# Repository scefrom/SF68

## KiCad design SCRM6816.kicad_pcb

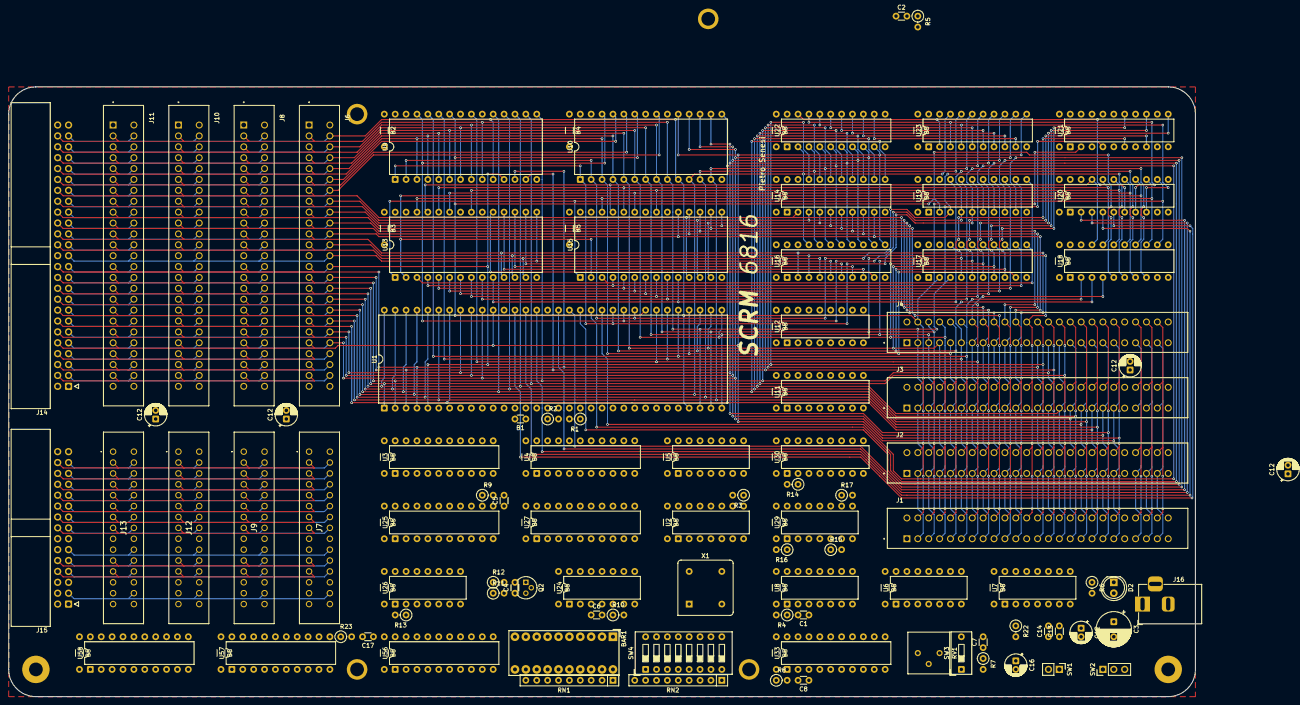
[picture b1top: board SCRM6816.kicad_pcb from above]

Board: 2 copper layers, 276.9 x 142.2 mm, 134 parts (0 on the bottom side), 190 nets.

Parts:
B1: 100nF; C_Disc_D3.0mm_W1.6mm_P2.54mm
B2, B3, B4, B5, B5#2, B5#3, B5#4, B5#5, B5#6, B5#7, B5#8, B5#9, B5#10, B5#11, B5#12, B5#13, B5#14, B5#15, B5#16, B5#17, B5#18, B5#19, B5#20, B5#21, B5#22, B5#23, B5#24, B5#25, B5#26, B5#27, B5#28, B5#29: C_Disc_D3.0mm_W1.6mm_P7.62mm
BAR1: HDSP-4830_2; HDSP-48xx
C1, C2, C5, C6, C8, C17: 22pF; C_Disc_D3.0mm_W1.6mm_P2.54mm
C3: 100uF; CP_Radial_D8.0mm_P3.50mm
C4: 220pF; C_Disc_D3.0mm_W1.6mm_P2.54mm
C7: 1uF; C_Disc_D3.0mm_W1.6mm_P2.54mm
C12, C12#2, C12#3, C12#4, C12#5, C16: 10uF; CP_Radial_D5.0mm_P2.00mm
C13: 330nF; C_Disc_D3.0mm_W1.6mm_P2.54mm
C14: 100nF; C_Disc_D3.0mm_W1.6mm_P2.54mm
D2: LED_Filled; LED_D5.0mm
J1: ramslot1; TE_1-5530843-6
J2: ramslot2; TE_1-5530843-6
J3: ramslot3; TE_1-5530843-6
J4: ramslot4; TE_1-5530843-6
J6: perslot1ad; TE_1-5530843-6
J7: perslot1c; 55308432
J8: perslot2ad; TE_1-5530843-6
J9: perslot2c; 55308432
J10: perslot3ad; TE_1-5530843-6
J11: perslot4ad; TE_1-5530843-6
J12: perslot3c; 55308432
J13: perslot4c; 55308432
J14: peridcad; IDC-Header_2x25_P2.54mm_Horizontal
J15: peridcc; IDC-Header_2x15_P2.54mm_Horizontal
J16: pwrjack; BarrelJack_Horizontal
M2, M2#2, M2#3, M2#4, M2#5, M2#6: MountingHole_3.2mm_M3_Pad
Q2: NPN; TO-92
R1, R2, R3, R8, R13, R14: 4k7; R_Axial_DIN0207_L6.3mm_D2.5mm_P2.54mm_Vertical
R4: 20k; R_Axial_DIN0207_L6.3mm_D2.5mm_P2.54mm_Vertical
R5, R23: 1k22; R_Axial_DIN0207_L6.3mm_D2.5mm_P2.54mm_Vertical
R6, R7: 1k; R_Axial_DIN0207_L6.3mm_D2.5mm_P2.54mm_Vertical
R9, R10: 2k; R_Axial_DIN0207_L6.3mm_D2.5mm_P2.54mm_Vertical
R11, R12, R15, R16, R17: 10k; R_Axial_DIN0207_L6.3mm_D2.5mm_P2.54mm_Vertical
R22: 14k7; R_Axial_DIN0207_L6.3mm_D2.5mm_P2.54mm_Vertical
RN1: 1k; R_Array_SIP9
RN2: 10k; R_Array_SIP9
RV1: 5k; Potentiometer_Bourns_3386P_Vertical
SW1: ressw; PinHeader_1x02_P2.54mm_Vertical
SW2: pwrsw; PinHeader_1x03_P2.54mm_Vertical
SW3: timersw; SW_DIP_SPSTx01_Slide_9.78x4.72mm_W7.62mm_P2.54mm
SW4: SW_DIP_x08; SW_DIP_SPSTx08_Slide_9.78x22.5mm_W7.62mm_P2.54mm
U1: 68HC000P16; DIP-64_W22.86mm
U2: 74HC04; DIP-14_W7.62mm
U3, U4, U21, U56: 74HC688; DIP-20_W7.62mm
U5: 74HC4075; DIP-14_W7.62mm
U6, U29: 74HC32; DIP-14_W7.62mm
U7, U26: 74HC14; DIP-14_W7.62mm
U8: 74HC05; DIP-14_W7.62mm
U9, U10: 28C256; DIP-28_W15.24mm
U11, U12: 74HC157; DIP-16_W7.62mm
U13, U15: AS7C256C-15PCN; DIP-28_W15.24mm
U14, U16: 74HC245; DIP-20_W7.62mm
U17, U18, U19, U20, U23, U27, U33, U58: 74HC541; DIP-20_W7.62mm
U22, U57: 74HC573; DIP-20_W7.62mm
U24: 74HC08; DIP-14_W7.62mm
U25: 74HC273; DIP-20_W7.62mm
U30: 74HC139; DIP-16_W7.62mm
X1: CXO_DIP8_16MHz; Oscillator_DIP-8

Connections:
+5V: B1.1, B2.1, B3.1, B4.1, B5.1, B5#2.1, B5#3.1, B5#4.1, B5#5.1, B5#6.1, B5#7.1, B5#8.1, B5#9.1, B5#10.1, B5#11.1, B5#12.1, B5#13.1, B5#14.1, B5#15.1, B5#16.1, B5#17.1, B5#18.1, B5#19.1, B5#20.1, B5#21.1, B5#22.1, B5#23.1, B5#24.1, B5#25.1, B5#26.1, B5#27.1, B5#28.1, B5#29.1, C3.1, C12.1, C12#2.1, C12#3.1, C12#4.1, C12#5.1, C13.2, C14.2, D2.2 (A), J1.41, J1.42, J2.41, J2.42, J3.41, J3.42, J4.41, J4.42, J7.17, J7.18, J7.19, J9.17, J9.18, J9.19, J12.17, J12.18, J12.19, J13.17, J13.18, J13.19, J15.12, J15.13, J15.14, R1.1, R2.1, R3.1, R8.1, R13.1, R14.1, R22.1, RN2.1 (common), SW2.2 (B), U1.12 (BGACK), U1.13 (BR), U1.14 (VCC), U1.21 (VPA), U1.22 (BERR), U1.25 (IPL0), U1.49 (VCC), U2.14 (VCC), U3.18 (R7), U3.20 (VCC), U4.3 (R0), U4.5 (R1), U4.7 (R2), U4.9 (R3), U4.12 (R4), U4.14 (R5), U4.16 (R6), U4.18 (R7), U4.20 (VCC), U5.14 (VDD), U6.14 (VCC), U7.14 (VCC), U8.14 (VCC), U9.28 (VCC), U10.28 (VCC), U11.10 (I1c), U11.16 (VCC), U12.3 (I1a), U12.5 (I0b), U12.10 (I1c), U12.11 (I0c), U12.13 (I1d), U12.14 (I0d), U12.16 (VCC), U13.28 (VCC), U14.20 (VCC), U15.28 (VCC), U16.20 (VCC), U17.20 (VCC), U18.9 (A7), U18.20 (VCC), U19.20 (VCC), U20.9 (A7), U20.20 (VCC), U21.20 (VCC), U22.20 (VCC), U23.20 (VCC), U24.14 (VCC), U25.18 (D7), U25.20 (VCC), U26.14 (VCC), U27.8 (A6), U27.20 (VCC), U29.14 (VCC), U30.16 (VCC), U33.8 (A6), U33.20 (VCC), U56.3 (R0), U56.5 (R1), U56.7 (R2), U56.9 (R3), U56.12 (R4), U56.14 (R5), U56.16 (R6), U56.20 (VCC), U57.20 (VCC)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
/AC.~D: J7.5, J9.5, J12.5, J13.5, J15.26, U1.27 (FC1), U24.2, U29.4
/AC.~P: J7.3, J9.3, J12.3, J13.3, J15.28, U1.28 (FC0), U24.1, U29.10
/AC.~U: J7.7, J9.7, J12.7, J13.7, J15.24, U1.26 (FC2), U3.17 (P7)
/A_{1}: J1.4, J2.4, J3.4, J4.4, J6.4, J8.4, J10.4, J11.4, J14.47, U1.29 (A1), U9.10 (A0), U10.10 (A0), U17.2 (A0), U21.2 (P0), U56.2 (P0)
/A_{2}: J1.3, J2.3, J3.3, J4.3, J6.3, J8.3, J10.3, J11.3, J14.48, U1.30 (A2), U9.9 (A1), U10.9 (A1), U17.3 (A1), U21.4 (P1), U56.4 (P1)
/A_{3}: J1.6, J2.6, J3.6, J4.6, J6.6, J8.6, J10.6, J11.6, J14.45, U1.31 (A3), U9.8 (A2), U10.8 (A2), U17.4 (A2), U21.6 (P2), U56.6 (P2)
/A_{4}: J1.5, J2.5, J3.5, J4.5, J6.5, J8.5, J10.5, J11.5, J14.46, U1.32 (A4), U9.7 (A3), U10.7 (A3), U17.5 (A3), U21.8 (P3), U56.8 (P3)
/A_{5}: J1.8, J2.8, J3.8, J4.8, J6.8, J8.8, J10.8, J11.8, J14.43, U1.33 (A5), U9.6 (A4), U10.6 (A4), U17.6 (A4), U21.11 (P4), U56.11 (P4)
/A_{6}: J1.7, J2.7, J3.7, J4.7, J6.7, J8.7, J10.7, J11.7, J14.44, U1.34 (A6), U9.5 (A5), U10.5 (A5), U17.7 (A5), U21.13 (P5), U56.13 (P5)
/A_{7}: J1.10, J2.10, J3.10, J4.10, J6.10, J8.10, J10.10, J11.10, J14.41, U1.35 (A7), U9.4 (A6), U10.4 (A6), U17.8 (A6), U21.15 (P6), U56.15 (P6)
/A_{8}: J1.9, J2.9, J3.9, J4.9, J6.9, J8.9, J10.9, J11.9, J14.42, U1.36 (A8), U4.2 (P0), U9.3 (A7), U10.3 (A7), U17.9 (A7)
/A_{9}: J1.12, J2.12, J3.12, J4.12, J6.12, J8.12, J10.12, J11.12, J14.39, U1.37 (A9), U4.4 (P1), U9.25 (A8), U10.25 (A8), U18.2 (A0)
/A_{10}: J1.11, J2.11, J3.11, J4.11, J6.11, J8.11, J10.11, J11.11, J14.40, U1.38 (A10), U4.6 (P2), U9.24 (A9), U10.24 (A9), U18.3 (A1)
/A_{11}: J1.14, J2.14, J3.14, J4.14, J6.14, J8.14, J10.14, J11.14, J14.37, U1.39 (A11), U4.8 (P3), U9.21 (A10), U10.21 (A10), U18.4 (A2)
/A_{12}: U1.40 (A12), U4.11 (P4), U9.23 (A11), U10.23 (A11), U18.5 (A3), U19.2 (A0)
/A_{13}: U1.41 (A13), U4.13 (P5), U9.2 (A12), U10.2 (A12), U18.6 (A4), U19.3 (A1)
/A_{14}: U1.42 (A14), U4.15 (P6), U9.26 (A13), U10.26 (A13), U18.7 (A5), U19.4 (A2)
/A_{15}: U1.43 (A15), U4.17 (P7), U9.1 (A14), U10.1 (A14), U18.8 (A6), U19.5 (A3)
/A_{16}: U1.44 (A16), U2.3, U5.2, U5.4, U19.6 (A4)
/A_{17}: U1.45 (A17), U3.2 (P0), U19.7 (A5)
/A_{18}: U1.46 (A18), U3.4 (P1), U19.8 (A6)
/A_{19}: U1.47 (A19), U3.6 (P2), U19.9 (A7)
/A_{20}: U1.48 (A20), U3.8 (P3), U20.2 (A0)
/A_{21}: U1.50 (A21), U3.11 (P4), U20.3 (A1)
/A_{22}: U1.51 (A22), U3.13 (P5), U20.4 (A2)
/A_{23}: U1.52 (A23), U3.15 (P6), U20.5 (A3)
/BE.I: C6.1, U3.1 (G), U24.3, U26.9
/BE.~ET: U5.10, U11.1 (S), U12.1 (S)
/BE.~E: U5.6, U6.2, U6.4, U7.3
/BE.~IO: J6.46, J8.46, J10.46, J11.46, J14.5, U5.9, U21.17 (P7), U56.17 (P7)
/BE.~M: J6.45, J8.45, J10.45, J11.45, J14.6, U2.2, U11.3 (I1a), U11.6 (I1b), U30.14 (A0)
/CLK: J7.28, J9.28, J12.28, J13.28, J15.3, U1.15 (CLK), X1.5 (OUT)
/DIR.~R: J6.47, J8.47, J10.47, J11.47, J14.4, U7.8, U9.22 (~OE), U10.22 (~OE), U11.14 (I0d), U23.1 (G1), U29.12, U58.1 (G1)
/DIR.~W: J6.48, J8.48, J10.48, J11.48, J14.3, U1.9 (R/W), U6.10, U6.13, U7.9, U9.27 (~WE), U10.27 (~WE), U11.11 (I0c), U14.1 (A->B), U16.1 (A->B), U29.2
/DRD: J1.43, J2.43, J3.43, J4.43, J7.21, J9.21, J12.21, J13.21, J15.10, R3.2, U7.5, U8.2
/DS.~L: J1.47, J2.47, J3.47, J4.47, J6.43, J8.43, J10.43, J11.43, J14.8, U1.8 (LDS), U6.1, U11.2 (I0a)
/DS.~U: J1.48, J2.48, J3.48, J4.48, J6.44, J8.44, J10.44, J11.44, J14.7, U1.7 (UDS), U6.5, U11.5 (I0b), U21.1 (G), U56.1 (G)
/D_{0}: J1.26, J2.26, J3.26, J4.26, J6.28, J8.28, J10.28, J11.28, J14.23, U1.5 (D0), U9.11 (D0), U14.18 (B0), U27.18 (Y0)
/D_{1}: J1.25, J2.25, J3.25, J4.25, J6.27, J8.27, J10.27, J11.27, J14.24, U1.4 (D1), U9.12 (D1), U14.17 (B1), U27.17 (Y1)
/D_{2}: J1.28, J2.28, J3.28, J4.28, J6.30, J8.30, J10.30, J11.30, J14.21, U1.3 (D2), U9.13 (D2), U14.16 (B2), U27.16 (Y2)
/D_{3}: J1.27, J2.27, J3.27, J4.27, J6.29, J8.29, J10.29, J11.29, J14.22, U1.2 (D3), U9.15 (D3), U14.15 (B3), U27.15 (Y3)
/D_{4}: J1.30, J2.30, J3.30, J4.30, J6.32, J8.32, J10.32, J11.32, J14.19, U1.1 (D4), U9.16 (D4), U14.14 (B4), U27.14 (Y4)
/D_{5}: J1.29, J2.29, J3.29, J4.29, J6.31, J8.31, J10.31, J11.31, J14.20, U1.64 (D5), U9.17 (D5), U14.13 (B5), U27.13 (Y5)
/D_{6}: J1.32, J2.32, J3.32, J4.32, J6.34, J8.34, J10.34, J11.34, J14.17, U1.63 (D6), U9.18 (D6), U14.12 (B6), U27.12 (Y6)
/D_{7}: J1.31, J2.31, J3.31, J4.31, J6.33, J8.33, J10.33, J11.33, J14.18, U1.62 (D7), U9.19 (D7), U14.11 (B7), U27.11 (Y7)
/D_{8}: J1.34, J2.34, J3.34, J4.34, J6.36, J8.36, J10.36, J11.36, J14.15, U1.61 (D8), U10.11 (D0), U16.18 (B0), U22.2 (D0), U23.18 (Y0), U57.2 (D0), U58.18 (Y0)
/D_{9}: J1.33, J2.33, J3.33, J4.33, J6.35, J8.35, J10.35, J11.35, J14.16, U1.60 (D9), U10.12 (D1), U16.17 (B1), U22.3 (D1), U23.17 (Y1), U57.3 (D1), U58.17 (Y1)
/D_{10}: J1.36, J2.36, J3.36, J4.36, J6.38, J8.38, J10.38, J11.38, J14.13, U1.59 (D10), U10.13 (D2), U16.16 (B2), U22.4 (D2), U23.16 (Y2), U57.4 (D2), U58.16 (Y2)
/D_{11}: J1.35, J2.35, J3.35, J4.35, J6.37, J8.37, J10.37, J11.37, J14.14, U1.58 (D11), U10.15 (D3), U16.15 (B3), U22.5 (D3), U23.15 (Y3), U57.5 (D3), U58.15 (Y3)
/D_{12}: J1.38, J2.38, J3.38, J4.38, J6.40, J8.40, J10.40, J11.40, J14.11, U1.57 (D12), U10.16 (D4), U16.14 (B4), U22.6 (D4), U23.14 (Y4), U57.6 (D4), U58.14 (Y4)
/D_{13}: J1.37, J2.37, J3.37, J4.37, J6.39, J8.39, J10.39, J11.39, J14.12, U1.56 (D13), U10.17 (D5), U16.13 (B5), U22.7 (D5), U23.13 (Y5), U57.7 (D5), U58.13 (Y5)
/D_{14}: J1.40, J2.40, J3.40, J4.40, J6.42, J8.42, J10.42, J11.42, J14.9, U1.55 (D14), U10.18 (D6), U16.12 (B6), U22.8 (D6), U23.12 (Y6), U57.8 (D6), U58.12 (Y6)
/D_{15}: J1.39, J2.39, J3.39, J4.39, J6.41, J8.41, J10.41, J11.41, J14.10, U1.54 (D15), U10.19 (D7), U16.11 (B7), U22.9 (D7), U23.11 (Y7), U57.9 (D7), U58.11 (Y7)
/E_{0}: J1.13, J2.13, J3.13, J4.13, J6.13, J8.13, J10.13, J11.13, J14.38, U14.2 (A0), U15.11 (D0)
/E_{1}: J1.16, J2.16, J3.16, J4.16, J6.16, J8.16, J10.16, J11.16, J14.35, U14.3 (A1), U15.12 (D1)
/E_{2}: J1.15, J2.15, J3.15, J4.15, J6.15, J8.15, J10.15, J11.15, J14.36, U14.4 (A2), U15.13 (D2)
/E_{3}: J1.18, J2.18, J3.18, J4.18, J6.18, J8.18, J10.18, J11.18, J14.33, U14.5 (A3), U15.15 (D3)
/E_{4}: J1.17, J2.17, J3.17, J4.17, J6.17, J8.17, J10.17, J11.17, J14.34, U14.6 (A4), U15.16 (D4)
/E_{5}: J1.20, J2.20, J3.20, J4.20, J6.20, J8.20, J10.20, J11.20, J14.31, R15.1, U14.7 (A5), U15.17 (D5)
/E_{6}: J1.19, J2.19, J3.19, J4.19, J6.19, J8.19, J10.19, J11.19, J14.32, R16.1, U14.8 (A6), U15.18 (D6)
/E_{7}: J1.22, J2.22, J3.22, J4.22, J6.22, J8.22, J10.22, J11.22, J14.29, R17.1, U14.9 (A7), U15.19 (D7)
/E_{8}: J1.21, J2.21, J3.21, J4.21, J6.21, J8.21, J10.21, J11.21, J14.30, U13.11 (D0), U16.2 (A0)
/E_{9}: J1.24, J2.24, J3.24, J4.24, J6.24, J8.24, J10.24, J11.24, J14.27, U13.12 (D1), U16.3 (A1)
/E_{10}: J6.23, J8.23, J10.23, J11.23, J14.28, U13.13 (D2), U16.4 (A2), U30.3 (A1)
/E_{11}: J6.26, J8.26, J10.26, J11.26, J14.25, U13.15 (D3), U16.5 (A3), U30.2 (A0)
/E_{12}: U13.16 (D4), U16.6 (A4)
/E_{13}: J7.4, J9.4, J12.4, J13.4, J15.27, U13.17 (D5), U16.7 (A5), U29.5
/E_{14}: J7.6, J9.6, J12.6, J13.6, J15.25, U13.18 (D6), U16.8 (A6), U29.1
/E_{15}: J7.8, J9.8, J12.8, J13.8, J15.23, U13.19 (D7), U16.9 (A7), U29.9
/IBSY: J7.20, J9.20, J12.20, J13.20, J15.11, R12.1, U25.19 (Q7), U26.3, U33.19 (G2)
/IRQ_{0}: J7.10, J9.10, J12.10, J13.10, J15.21, U25.3 (D0), U33.18 (Y0)
/IRQ_{1}: J7.9, J9.9, J12.9, J13.9, J15.22, U25.4 (D1), U33.17 (Y1)
/IRQ_{2}: J7.12, J9.12, J12.12, J13.12, J15.19, U25.7 (D2), U33.16 (Y2)
/IRQ_{3}: J7.11, J9.11, J12.11, J13.11, J15.20, U25.8 (D3), U33.15 (Y3)
/IRQ_{4}: J7.14, J9.14, J12.14, J13.14, J15.17, U25.13 (D4), U33.14 (Y4)
/IRQ_{5}: J7.13, J9.13, J12.13, J13.13, J15.18, U25.14 (D5), U33.13 (Y5)
/IRQ_{6}: J7.16, J9.16, J12.16, J13.16, J15.15, U25.17 (D6), U33.12 (Y6)
/IRQ_{7}: J7.15, J9.15, J12.15, J13.15, J15.16, R13.2, U26.1, U33.11 (Y7)
/atu/EA_{0}: U13.10 (A0), U15.10 (A0), U17.18 (Y0), U19.18 (Y0)
/atu/EA_{1}: U13.9 (A1), U15.9 (A1), U17.17 (Y1), U19.17 (Y1)
/atu/EA_{2}: U13.8 (A2), U15.8 (A2), U17.16 (Y2), U19.16 (Y2)
/atu/EA_{3}: U13.7 (A3), U15.7 (A3), U17.15 (Y3), U19.15 (Y3)
/atu/EA_{4}: U13.6 (A4), U15.6 (A4), U17.14 (Y4), U19.14 (Y4)
/atu/EA_{5}: U13.5 (A5), U15.5 (A5), U17.13 (Y5), U19.13 (Y5)
/atu/EA_{6}: U13.4 (A6), U15.4 (A6), U17.12 (Y6), U19.12 (Y6)
/atu/EA_{7}: U13.3 (A7), U15.3 (A7), U17.11 (Y7), U19.11 (Y7)
/atu/EA_{8}: U13.25 (A8), U15.25 (A8), U18.18 (Y0), U20.18 (Y0)
/atu/EA_{9}: U13.24 (A9), U15.24 (A9), U18.17 (Y1), U20.17 (Y1)
/atu/EA_{10}: U13.21 (A10), U15.21 (A10), U18.16 (Y2), U20.16 (Y2)
/atu/EA_{11}: U13.23 (A11), U15.23 (A11), U18.15 (Y3), U20.15 (Y3)
/atu/EA_{12}: U13.2 (A12), U15.2 (A12), U18.14 (Y4), U20.14 (Y4)
/atu/EA_{13}: U13.26 (A13), U15.26 (A13), U18.13 (Y5), U20.13 (Y5)
/atu/EA_{14}: U13.1 (A14), U15.1 (A14), U18.12 (Y6), U20.12 (Y6)
/atu/MOD.~R: U12.7 (Zb), U19.1 (G1), U19.19 (G2), U20.1 (G1), U20.19 (G2)
/atu/MOD.~S: U12.4 (Za), U14.19 (CE), U16.19 (CE), U17.1 (G1), U17.19 (G2), U18.1 (G1), U18.19 (G2)
/atu/PN_{0}: U20.6 (A4), U22.19 (Q0), U23.2 (A0)
/atu/PN_{1}: U20.7 (A5), U22.18 (Q1), U23.3 (A1)
/atu/PN_{2}: U20.8 (A6), U22.17 (Q2), U23.4 (A2)
/atu/PN_{3}: U22.16 (Q3), U23.5 (A3)
/atu/PN_{4}: U22.15 (Q4), U23.6 (A4)
/atu/PN_{5}: U22.14 (Q5), U23.7 (A5)
/atu/PN_{6}: U22.13 (Q6), U23.8 (A6)
/atu/PN_{7}: U22.12 (Q7), U23.9 (A7)
/atu/pidreg/LD: C2.1, U2.8
/atu/pidreg/~S: U6.9, U21.19 (P=R), U23.19 (G2)
/atu/~LS: U11.4 (Za), U15.20 (CE)
/atu/~R: U11.12 (Zd), U13.22 (OE), U15.22 (OE)
/atu/~US: U11.7 (Zb), U13.20 (CE)
/atu/~W: U11.9 (Zc), U13.27 (WE), U15.27 (WE)
/decoder/~IOS: U2.5, U4.19 (P=R), U5.1
/decoder/~SAS: U2.1, U3.19 (P=R), U5.5, U5.8, U5.12
/ram/PDIR.~R: J1.45, J2.45, J3.45, J4.45, U29.11
/ram/PDIR.~W: J1.46, J2.46, J3.46, J4.46, U29.3
/ram/~BKE_{0}: J1.44, U30.4 (O0)
/ram/~BKE_{1}: J2.44, U30.5 (O1)
/ram/~BKE_{2}: J3.44, U30.6 (O2)
/ram/~BKE_{3}: J4.44, U30.7 (O3)
/rom/~LS: U6.3, U9.20 (~CS)
/rom/~US: U6.6, U10.20 (~CS)
/statusreg/LD: C17.1, U2.10
/statusreg/SI_{0}: RN2.2 (R1), SW4.8, U58.2 (A0)
/statusreg/SI_{1}: RN2.3 (R2), SW4.7, U58.3 (A1)
/statusreg/SI_{2}: RN2.4 (R3), SW4.6, U58.4 (A2)
/statusreg/SI_{3}: RN2.5 (R4), SW4.5, U58.5 (A3)
/statusreg/SI_{4}: RN2.6 (R5), SW4.4, U58.6 (A4)
/statusreg/SI_{5}: RN2.7 (R6), SW4.3, U58.7 (A5)
/statusreg/SI_{6}: RN2.8 (R7), SW4.2, U58.8 (A6)
/statusreg/SI_{7}: RN2.9 (R8), SW4.1, U58.9 (A7)
/statusreg/S_{0}: BAR1.1 (A), U57.19 (Q0)
/statusreg/S_{1}: BAR1.2 (A), U57.18 (Q1)
/statusreg/S_{2}: BAR1.3 (A), U57.17 (Q2)
/statusreg/S_{3}: BAR1.4 (A), U57.16 (Q3)
/statusreg/S_{4}: BAR1.5 (A), U57.15 (Q4)
/statusreg/S_{5}: BAR1.6 (A), U57.14 (Q5)
/statusreg/S_{6}: BAR1.7 (A), U57.13 (Q6)
/statusreg/S_{7}: BAR1.8 (A), U57.12 (Q7)
/statusreg/~S: U6.12, U56.19 (P=R), U58.19 (G2)
/~DRD: U1.10 (DTACK), U7.6
/~HALT: J7.23, J9.23, J12.23, J13.23, J15.8, R2.2, U1.17 (HALT), U8.6
/~I_{1}: U1.24 (IPL1), U26.10
/~I_{2}: U1.23 (IPL2), U26.12
/~RES: J7.24, J9.24, J12.24, J13.24, J15.7, R1.2, U1.18 (RESET), U8.4, U24.9
/~RIH: J7.22, J9.22, J12.22, J13.22, J15.9, R14.2, U30.13 (A1)
GND: B1.2, B2.2, B3.2, B4.2, B5.2, B5#2.2, B5#3.2, B5#4.2, B5#5.2, B5#6.2, B5#7.2, B5#8.2, B5#9.2, B5#10.2, B5#11.2, B5#12.2, B5#13.2, B5#14.2, B5#15.2, B5#16.2, B5#17.2, B5#18.2, B5#19.2, B5#20.2, B5#21.2, B5#22.2, B5#23.2, B5#24.2, B5#25.2, B5#26.2, B5#27.2, B5#28.2, B5#29.2, C3.2, C4.1, C5.1, C7.1, C12.2, C12#2.2, C12#3.2, C12#4.2, C12#5.2, C13.1, C14.1, C16.2, J1.1, J1.2, J1.23, J1.49, J1.50, J2.1, J2.2, J2.23, J2.49, J2.50, J3.1, J3.2, J3.23, J3.49, J3.50, J4.1, J4.2, J4.23, J4.49, J4.50, J6.1, J6.2, J6.25, J6.49, J6.50, J7.1, J7.2, J7.25, J7.26, J7.27, J7.29, J7.30, J8.1, J8.2, J8.25, J8.49, J8.50, J9.1, J9.2, J9.25, J9.26, J9.27, J9.29, J9.30, J10.1, J10.2, J10.25, J10.49, J10.50, J11.1, J11.2, J11.25, J11.49, J11.50, J12.1, J12.2, J12.25, J12.26, J12.27, J12.29, J12.30, J13.1, J13.2, J13.25, J13.26, J13.27, J13.29, J13.30, J14.1, J14.2, J14.26, J14.49, J14.50, J15.1, J15.2, J15.4, J15.5, J15.6, J15.29, J15.30, J16.2, J16.3, M2.1, M2#2.1, M2#3.1, M2#4.1, M2#5.1, M2#6.1, Q2.3 (E), R4.2, R5.2, R6.2, R10.2, R15.2, R16.2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
unnamed: C1.1, U7.4
unnamed: C1.2, R4.1, U8.1
unnamed: C6.2, R10.1, U24.4
unnamed: C8.1, R7.1, U7.10
unnamed: C16.1, R22.2, SW1.2, U7.1
unnamed: D2.1 (K), R6.1
unnamed: Q2.2 (B), R11.2
unnamed: C4.2, Q2.1 (C), R12.2, U26.5
unnamed: R7.2, RV1.1
unnamed: R9.1, U26.2
unnamed: R11.1, U26.4
unnamed: BAR1.20 (K), RN1.2 (R1)
unnamed: BAR1.19 (K), RN1.3 (R2)
unnamed: BAR1.18 (K), RN1.4 (R3)
unnamed: BAR1.17 (K), RN1.5 (R4)
unnamed: BAR1.16 (K), RN1.6 (R5)
unnamed: BAR1.15 (K), RN1.7 (R6)
unnamed: BAR1.14 (K), RN1.8 (R7)
unnamed: BAR1.13 (K), RN1.9 (R8)
unnamed: J16.1, SW2.3 (C)
unnamed: C7.2, RV1.2, SW3.2 (B), U7.11
unnamed: U2.4, U5.11
unnamed: U2.6, U5.3
unnamed: U2.9, U6.8
unnamed: U2.11, U6.11
unnamed: U7.2, U8.3, U8.5
unnamed: C2.2, R5.1, U22.11 (Load)
unnamed: U24.5, U24.8
unnamed: U24.10, U26.6
unnamed: U24.11, U29.13
unnamed: U24.12, U29.6
unnamed: U24.13, U29.8
unnamed: C5.2, R9.2, U25.11 (Cp)
unnamed: U25.2 (Q0), U27.2 (A0)
unnamed: U25.5 (Q1), U27.3 (A1)
unnamed: U25.6 (Q2), U27.4 (A2)
unnamed: U25.9 (Q3), U27.5 (A3)
unnamed: U25.12 (Q4), U27.6 (A4)
unnamed: U25.15 (Q5), U26.11
unnamed: U25.16 (Q6), U26.13
unnamed: U24.6, U25.1 (~Mr)
unnamed: U26.8, U27.1 (G1), U27.19 (G2)
unnamed: U30.1 (E), U30.10 (O2)
unnamed: C8.2, R8.2, U33.1 (G1)
unnamed: C17.2, R23.1, U57.11 (Load)

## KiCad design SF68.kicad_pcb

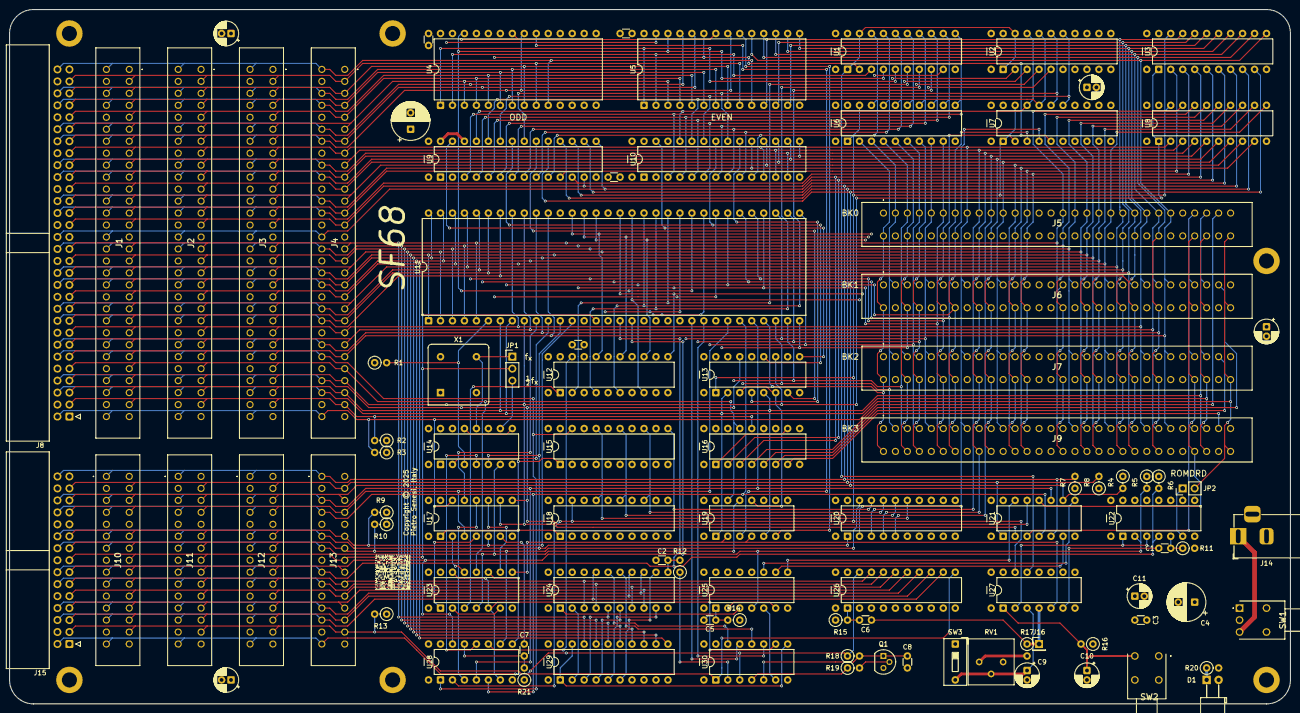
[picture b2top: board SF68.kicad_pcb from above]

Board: 4 copper layers, 271.8 x 147.3 mm, 129 parts (0 on the bottom side), 164 nets.

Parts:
C1, C8: 220pF; C_Disc_D3.0mm_W1.6mm_P2.54mm
C2, C5, C6, C7: 22pF; C_Disc_D3.0mm_W1.6mm_P2.54mm
C3: 100nF; C_Disc_D3.0mm_W1.6mm_P2.54mm
C4: 100uF; CP_Radial_D8.0mm_P3.50mm
C9, C10, C11: 10uF; CP_Radial_D5.0mm_P2.00mm
CB1, CB7, CB15, CB36: CP_Radial_D5.0mm_P2.00mm
CB2, CB3, CB14, CB16: C_Disc_D3.0mm_W1.6mm_P2.54mm
CB4, CB5, CB6, CB8, CB9, CB10, CB12, CB13, CB17, CB18, CB19, CB20, CB21, CB22, CB23, CB24, CB25, CB26, CB27, CB28, CB29, CB30, CB31, CB32, CB33, CB34, CB35: C_Disc_D3.0mm_W1.6mm_P7.62mm
CB11: CP_Radial_D8.0mm_P3.50mm
D1: LED_Filled; LED_D5.0mm_Horizontal_O3.81mm_Z3.0mm
J1: perslot4a; 55308437
J2: perslot3a; 55308437
J3: perslot2a; 55308437
J4: perslot1a; 55308437
J5: ramslot1; 55308437
J6: ramslot2; 55308437
J7: ramslot3; 55308437
J8: perslot5a; IDC-Header_2x30_P2.54mm_Horizontal
J9: ramslot4; 55308437
J10: perslot4b; 55308432
J11: perslot3b; 55308432
J12: perslot2b; 55308432
J13: perslot1b; 55308432
J14: pwrjack; BarrelJack_Horizontal
J15: perslot5b; IDC-Header_2x15_P2.54mm_Horizontal
J16: stprobe; PinHeader_1x01_P2.54mm_Vertical
JP1: Jumper_3_Bridged12; PinHeader_1x03_P2.54mm_Vertical
JP2: romrd; PinHeader_1x02_P2.54mm_Vertical
M1, M2, M3, M4, M5, M6: MountingHole_3.2mm_M3_DIN965_Pad
Q1: Q_NPN_CBE; TO-92
R1, R4, R7, R8, R18, R19: 10k; R_Axial_DIN0207_L6.3mm_D2.5mm_P2.54mm_Vertical
R2, R3, R5, R6, R9, R10, R13, R15, R21: 4k7; R_Axial_DIN0207_L6.3mm_D2.5mm_P2.54mm_Vertical
R11, R12, R14: 2k; R_Axial_DIN0207_L6.3mm_D2.5mm_P2.54mm_Vertical
R16: 14k7; R_Axial_DIN0207_L6.3mm_D2.5mm_P2.54mm_Vertical
R17, R20: 1k; R_Axial_DIN0207_L6.3mm_D2.5mm_P2.54mm_Vertical
RV1: 5k; Potentiometer_Bourns_3386P_Vertical
SW1: pwrsw; 800CSP1B6M6QE
SW2: ressw; 800SP9B6M6RE
SW3: timersw; SW_DIP_SPSTx01_Slide_9.78x4.72mm_W7.62mm_P2.54mm
U1, U2, U6, U7, U20, U26, U29: 74HC541; DIP-20_W7.62mm
U3, U8: 74HC245; DIP-20_W7.62mm
U4, U5: 28C256; DIP-28_W15.24mm
U9, U10: AS7C164A; DIP-28_W7.62mm
U11: 68HC000P10; DIP-64_W22.86mm
U12, U15, U18: 74HC688; DIP-20_W7.62mm
U13: 74HC157; DIP-16_W7.62mm
U14: 74HC74; DIP-14_W7.62mm
U16: 74HC139; DIP-16_W7.62mm
U17: 74HC04; DIP-14_W7.62mm
U19, U21, U23: 74HC32; DIP-14_W7.62mm
U22: 74HC05; DIP-14_W7.62mm
U24: 74HC273; DIP-20_W7.62mm
U25, U28: 74HC08; DIP-14_W7.62mm
U27, U30: 74HC14; DIP-14_W7.62mm
X1: CXO_DIP8; Oscillator_DIP-8

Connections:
+5V: C3.2, C4.1, C11.1, CB1.1, CB2.1, CB3.1, CB4.1, CB5.1, CB6.1, CB7.1, CB8.1, CB9.1, CB10.1, CB11.1, CB12.1, CB13.1, CB14.1, CB15.1, CB16.1, CB17.1, CB18.1, CB19.1, CB20.1, CB21.1, CB22.1, CB23.1, CB24.1, CB25.1, CB26.1, CB27.1, CB28.1, CB29.1, CB30.1, CB31.1, CB32.1, CB33.1, CB34.1, CB35.1, CB36.1, D1.2 (A), J1.1, J1.29, J1.59, J2.1, J2.29, J2.59, J3.1, J3.29, J3.59, J4.1, J4.29, J4.59, J5.1, J5.29, J5.59, J6.1, J6.29, J6.59, J7.1, J7.29, J7.59, J8.1, J8.31, J8.59, J9.1, J9.29, J9.59, J10.2, J10.30, J11.2, J11.30, J12.2, J12.30, J13.2, J13.30, J15.1, J15.29, R1.1, R2.1, R3.1, R5.1, R6.1, R9.1, R10.1, R13.1, R14.1, R15.1, R16.1, R21.1, SW1.2 (B), U1.20 (VCC), U2.6 (A4), U2.7 (A5), U2.8 (A6), U2.9 (A7), U2.20 (VCC), U3.20 (VCC), U4.28 (VCC), U5.28 (VCC), U6.20 (VCC), U7.6 (A4), U7.7 (A5), U7.8 (A6), U7.9 (A7), U7.20 (VCC), U8.20 (VCC), U9.26 (CE2), U9.28 (VCC), U10.26 (CE2), U10.28 (VCC), U11.14 (VCC), U11.21 (VPA), U11.22 (BERR), U11.25 (IPL0), U11.49 (VCC), U12.20 (VCC), U13.10 (I1c), U13.16 (VCC), U14.1 (~R), U14.10 (~S), U14.13 (~R), U14.14 (VCC), U15.3 (R0), U15.5 (R1), U15.7 (R2), U15.9 (R3), U15.12 (R4), U15.16 (R6), U15.18 (R7), U15.20 (VCC), U16.16 (VCC), U17.14 (VCC), U18.2 (P0), U18.3 (R0), U18.4 (P1), U18.5 (R1), U18.6 (P2), U18.7 (R2), U18.8 (P3), U18.9 (R3)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
/AC.~D: J10.7, J11.7, J12.7, J13.7, J15.24, U11.27 (FC1), U21.4, U28.5
/AC.~P: J10.5, J11.5, J12.5, J13.5, J15.26, U11.28 (FC0), U21.10, U28.4
/AC.~U: J10.8, J11.8, J12.8, J13.8, J15.23, U11.26 (FC2), U17.3
/AS: R1.2, U11.6 (AS), U14.3 (C)
/A_{1}: J1.2, J2.2, J3.2, J4.2, J5.2, J6.2, J7.2, J8.60, J9.2, U4.10 (A0), U5.10 (A0), U6.2 (A0), U11.29 (A1)
/A_{2}: J1.3, J2.3, J3.3, J4.3, J5.3, J6.3, J7.3, J8.57, J9.3, U4.9 (A1), U5.9 (A1), U6.3 (A1), U11.30 (A2)
/A_{3}: J1.5, J2.5, J3.5, J4.5, J5.5, J6.5, J7.5, J8.55, J9.5, U4.8 (A2), U5.8 (A2), U6.4 (A2), U11.31 (A3)
/A_{4}: J1.6, J2.6, J3.6, J4.6, J5.6, J6.6, J7.6, J8.56, J9.6, U4.7 (A3), U5.7 (A3), U6.5 (A3), U11.32 (A4)
/A_{5}: J1.7, J2.7, J3.7, J4.7, J5.7, J6.7, J7.7, J8.53, J9.7, U4.6 (A4), U5.6 (A4), U6.6 (A4), U11.33 (A5)
/A_{6}: J1.8, J2.8, J3.8, J4.8, J5.8, J6.8, J7.8, J8.54, J9.8, U4.5 (A5), U5.5 (A5), U6.7 (A5), U11.34 (A6)
/A_{7}: J1.9, J2.9, J3.9, J4.9, J5.9, J6.9, J7.9, J8.51, J9.9, U4.4 (A6), U5.4 (A6), U6.8 (A6), U11.35 (A7)
/A_{8}: J1.11, J2.11, J3.11, J4.11, J5.11, J6.11, J7.11, J8.49, J9.11, U4.3 (A7), U5.3 (A7), U6.9 (A7), U11.36 (A8), U15.2 (P0)
/A_{9}: J1.12, J2.12, J3.12, J4.12, J5.12, J6.12, J7.12, J8.50, J9.12, U4.25 (A8), U5.25 (A8), U7.2 (A0), U11.37 (A9), U15.4 (P1)
/A_{10}: J1.13, J2.13, J3.13, J4.13, J5.13, J6.13, J7.13, J8.47, J9.13, U4.24 (A9), U5.24 (A9), U7.3 (A1), U11.38 (A10), U15.6 (P2)
/A_{11}: J1.14, J2.14, J3.14, J4.14, J5.14, J6.14, J7.14, J8.48, J9.14, U4.21 (A10), U5.21 (A10), U7.4 (A2), U11.39 (A11), U15.8 (P3)
/A_{12}: U1.2 (A0), U4.23 (A11), U5.23 (A11), U7.5 (A3), U11.40 (A12), U15.11 (P4), U20.18 (Y0)
/A_{13}: U1.3 (A1), U4.2 (A12), U5.2 (A12), U11.41 (A13), U15.13 (P5), U18.13 (P5), U20.17 (Y1)
/A_{14}: U1.4 (A2), U4.26 (A13), U5.26 (A13), U11.42 (A14), U15.15 (P6), U18.15 (P6), U20.16 (Y2)
/A_{15}: U1.5 (A3), U4.1 (A14), U5.1 (A14), U11.43 (A15), U15.17 (P7), U18.17 (P7), U20.15 (Y3)
/A_{16}: U1.6 (A4), U11.44 (A16), U12.2 (P0)
/A_{17}: U1.7 (A5), U11.45 (A17), U12.4 (P1)
/A_{18}: U1.8 (A6), U11.46 (A18), U12.6 (P2)
/A_{19}: U1.9 (A7), U11.47 (A19), U12.8 (P3)
/A_{20}: U2.2 (A0), U11.48 (A20), U12.11 (P4)
/A_{21}: U2.3 (A1), U11.50 (A21), U12.13 (P5)
/A_{22}: U2.4 (A2), U11.51 (A22), U12.15 (P6)
/A_{23}: U2.5 (A3), U11.52 (A23), U12.17 (P7)
/BE.I: C5.1, U23.5, U23.13, U28.6, U30.9
/BE.~EE: U19.2, U19.4, U23.8, U27.5
/BE.~IO: J1.50, J2.50, J3.50, J4.50, J8.12, U15.19 (P=R), U28.1
/BE.~M: J1.51, J2.51, J3.51, J4.51, J8.9, U16.14 (A0), U19.13, U23.11
/BE.~PT: U3.19 (CE), U6.1 (G1), U6.19 (G2), U7.1 (G1), U7.19 (G2), U8.19 (CE), U13.1 (S), U18.19 (P=R), U27.13, U28.2
/CLK: J10.16, J11.16, J12.16, J13.16, J15.15, JP1.2 (C), U11.15 (CLK)
/DIR.~R: J1.54, J2.54, J3.54, J4.54, J8.8, U4.22 (~OE), U5.22 (~OE), U13.14 (I0d), U17.8, U21.12
/DIR.~W: J1.53, J2.53, J3.53, J4.53, J8.7, U3.1 (A->B), U4.27 (~WE), U5.27 (~WE), U8.1 (A->B), U11.9 (R/W), U13.11 (I0c), U17.9, U21.2
/DMA.G: J10.13, J11.13, J12.13, J13.13, J15.18, U14.6 (~Q), U19.12, U23.4
/DMA.~G: J10.11, J11.11, J12.11, J13.11, J15.20, U11.12 (BGACK), U14.5 (Q), U20.1 (G1)
/DMA.~R: J10.12, J11.12, J12.12, J13.12, J15.19, R9.2, U11.13 (BR), U17.5
/DMA.~SAS: J10.14, J11.14, J12.14, J13.14, J15.17, R10.2, U20.19 (G2), U28.9
/DRD: J1.60, J2.60, J3.60, J4.60, J5.60, J6.60, J7.60, J8.2, J9.60, JP2.2 (B), R3.2, U17.13
/DS.~L: J1.56, J2.56, J3.56, J4.56, J5.56, J6.56, J7.56, J8.6, J9.56, U11.8 (LDS), U13.2 (I0a), U19.1
/DS.~U: J1.55, J2.55, J3.55, J4.55, J5.55, J6.55, J7.55, J8.5, J9.55, U11.7 (UDS), U13.5 (I0b), U19.5
/D_{0}: J1.31, J2.31, J3.31, J4.31, J5.31, J6.31, J7.31, J8.29, J9.31, U4.11 (D0), U8.18 (B0), U11.5 (D0), U29.18 (Y0)
/D_{1}: J1.32, J2.32, J3.32, J4.32, J5.32, J6.32, J7.32, J8.30, J9.32, U4.12 (D1), U8.17 (B1), U11.4 (D1), U29.17 (Y1)
/D_{2}: J1.33, J2.33, J3.33, J4.33, J5.33, J6.33, J7.33, J8.27, J9.33, U4.13 (D2), U8.16 (B2), U11.3 (D2), U29.16 (Y2)
/D_{3}: J1.35, J2.35, J3.35, J4.35, J5.35, J6.35, J7.35, J8.25, J9.35, U4.15 (D3), U8.15 (B3), U11.2 (D3), U29.15 (Y3)
/D_{4}: J1.36, J2.36, J3.36, J4.36, J5.36, J6.36, J7.36, J8.26, J9.36, U4.16 (D4), U8.14 (B4), U11.1 (D4), U29.14 (Y4)
/D_{5}: J1.37, J2.37, J3.37, J4.37, J5.37, J6.37, J7.37, J8.23, J9.37, U4.17 (D5), U8.13 (B5), U11.64 (D5), U29.13 (Y5)
/D_{6}: J1.38, J2.38, J3.38, J4.38, J5.38, J6.38, J7.38, J8.24, J9.38, U4.18 (D6), U8.12 (B6), U11.63 (D6), U29.12 (Y6)
/D_{7}: J1.39, J2.39, J3.39, J4.39, J5.39, J6.39, J7.39, J8.21, J9.39, U4.19 (D7), U8.11 (B7), U11.62 (D7), U29.11 (Y7)
/D_{8}: J1.41, J2.41, J3.41, J4.41, J5.41, J6.41, J7.41, J8.19, J9.41, U3.18 (B0), U5.11 (D0), U11.61 (D8)
/D_{9}: J1.42, J2.42, J3.42, J4.42, J5.42, J6.42, J7.42, J8.20, J9.42, U3.17 (B1), U5.12 (D1), U11.60 (D9)
/D_{10}: J1.43, J2.43, J3.43, J4.43, J5.43, J6.43, J7.43, J8.17, J9.43, U3.16 (B2), U5.13 (D2), U11.59 (D10)
/D_{11}: J1.44, J2.44, J3.44, J4.44, J5.44, J6.44, J7.44, J8.18, J9.44, U3.15 (B3), U5.15 (D3), U11.58 (D11)
/D_{12}: J1.45, J2.45, J3.45, J4.45, J5.45, J6.45, J7.45, J8.15, J9.45, U3.14 (B4), U5.16 (D4), U11.57 (D12)
/D_{13}: J1.47, J2.47, J3.47, J4.47, J5.47, J6.47, J7.47, J8.13, J9.47, U3.13 (B5), U5.17 (D5), U11.56 (D13)
/D_{14}: J1.48, J2.48, J3.48, J4.48, J5.48, J6.48, J7.48, J8.14, J9.48, U3.12 (B6), U5.18 (D6), U11.55 (D14)
/D_{15}: J1.49, J2.49, J3.49, J4.49, J5.49, J6.49, J7.49, J8.11, J9.49, U3.11 (B7), U5.19 (D7), U11.54 (D15)
/E_{0}: J1.15, J2.15, J3.15, J4.15, J5.15, J6.15, J7.15, J8.45, J9.15, U8.2 (A0), U10.11 (D0), U20.2 (A0)
/E_{1}: J1.17, J2.17, J3.17, J4.17, J5.17, J6.17, J7.17, J8.43, J9.17, U8.3 (A1), U10.12 (D1), U20.3 (A1)
/E_{2}: J1.18, J2.18, J3.18, J4.18, J5.18, J6.18, J7.18, J8.44, J9.18, U8.4 (A2), U10.13 (D2), U20.4 (A2)
/E_{3}: J1.19, J2.19, J3.19, J4.19, J5.19, J6.19, J7.19, J8.41, J9.19, U8.5 (A3), U10.15 (D3), U20.5 (A3)
/E_{4}: J1.20, J2.20, J3.20, J4.20, J5.20, J6.20, J7.20, J8.42, J9.20, U8.6 (A4), U10.16 (D4)
/E_{5}: J1.21, J2.21, J3.21, J4.21, J5.21, J6.21, J7.21, J8.39, J9.21, U8.7 (A5), U10.17 (D5)
/E_{6}: J1.23, J2.23, J3.23, J4.23, J5.23, J6.23, J7.23, J8.37, J9.23, U8.8 (A6), U10.18 (D6)
/E_{7}: J1.24, J2.24, J3.24, J4.24, J5.24, J6.24, J7.24, J8.38, J9.24, U8.9 (A7), U10.19 (D7)
/E_{8}: J1.25, J2.25, J3.25, J4.25, J5.25, J6.25, J7.25, J8.35, J9.25, U3.2 (A0), U9.11 (D0)
/E_{9}: J1.26, J2.26, J3.26, J4.26, J5.26, J6.26, J7.26, J8.36, J9.26, U3.3 (A1), U9.12 (D1)
/E_{10}: J1.27, J2.27, J3.27, J4.27, J8.33, U3.4 (A2), U9.13 (D2), U16.3 (A1)
/E_{11}: J1.30, J2.30, J3.30, J4.30, J8.32, U3.5 (A3), U9.15 (D3), U16.2 (A0)
/E_{12}: U3.6 (A4), U9.16 (D4)
/E_{13}: J10.1, J11.1, J12.1, J13.1, J15.30, R7.2, U3.7 (A5), U9.17 (D5), U21.5
/E_{14}: J10.4, J11.4, J12.4, J13.4, J15.27, R8.2, U3.8 (A6), U9.18 (D6), U21.1
/E_{15}: J10.6, J11.6, J12.6, J13.6, J15.25, R4.2, U3.9 (A7), U9.19 (D7), U21.9
/IBSY: J10.29, J11.29, J12.29, J13.29, J15.2, R18.1, U24.19 (Q7), U26.19 (G2), U30.3
/IRQ_{0}: J10.20, J11.20, J12.20, J13.20, J15.11, U24.3 (D0), U26.18 (Y0)
/IRQ_{1}: J10.19, J11.19, J12.19, J13.19, J15.12, U24.4 (D1), U26.17 (Y1)
/IRQ_{2}: J10.22, J11.22, J12.22, J13.22, J15.9, U24.7 (D2), U26.16 (Y2)
/IRQ_{3}: J10.24, J11.24, J12.24, J13.24, J15.7, U24.8 (D3), U26.15 (Y3)
/IRQ_{4}: J10.23, J11.23, J12.23, J13.23, J15.8, U24.13 (D4), U26.14 (Y4)
/IRQ_{5}: J10.26, J11.26, J12.26, J13.26, J15.5, U24.14 (D5), U26.13 (Y5)
/IRQ_{6}: J10.25, J11.25, J12.25, J13.25, J15.6, U24.17 (D6), U26.12 (Y6)
/IRQ_{7}: J10.28, J11.28, J12.28, J13.28, J15.3, R13.2, U26.11 (Y7), U30.1
/decoder/SAS: U17.2, U23.12
/decoder/~SAS: U15.1 (G), U17.1, U18.1 (G), U23.10, U28.8
/mmu/EA_{0}: U1.18 (Y0), U6.18 (Y0), U9.10 (A0), U10.10 (A0)
/mmu/EA_{1}: U1.17 (Y1), U6.17 (Y1), U9.9 (A1), U10.9 (A1)
/mmu/EA_{2}: U1.16 (Y2), U6.16 (Y2), U9.8 (A2), U10.8 (A2)
/mmu/EA_{3}: U1.15 (Y3), U6.15 (Y3), U9.7 (A3), U10.7 (A3)
/mmu/EA_{4}: U1.14 (Y4), U6.14 (Y4), U9.6 (A4), U10.6 (A4)
/mmu/EA_{5}: U1.13 (Y5), U6.13 (Y5), U9.5 (A5), U10.5 (A5)
/mmu/EA_{6}: U1.12 (Y6), U6.12 (Y6), U9.4 (A6), U10.4 (A6)
/mmu/EA_{7}: U1.11 (Y7), U6.11 (Y7), U9.3 (A7), U10.3 (A7)
/mmu/EA_{8}: U2.18 (Y0), U7.18 (Y0), U9.25 (A8), U10.25 (A8)
/mmu/EA_{9}: U2.17 (Y1), U7.17 (Y1), U9.24 (A9), U10.24 (A9)
/mmu/EA_{10}: U2.16 (Y2), U7.16 (Y2), U9.21 (A10), U10.21 (A10)
/mmu/EA_{11}: U2.15 (Y3), U7.15 (Y3), U9.23 (A11), U10.23 (A11)
/mmu/buffers/S/~R: U1.1 (G1), U1.19 (G2), U2.1 (G1), U2.19 (G2), U27.12
/mmu/~LS: U10.20 (~CE), U13.4 (Za)
/mmu/~R: U9.22 (~OE), U10.22 (~OE), U13.12 (Zd)
/mmu/~US: U9.20 (~CE), U13.7 (Zb)
/mmu/~W: U9.27 (~WE), U10.27 (~WE), U13.9 (Zc)
/ram/PDIR.~R: J5.54, J6.54, J7.54, J9.54, U21.11
/ram/PDIR.~W: J5.53, J6.53, J7.53, J9.53, U21.3
/ram/~BKE_{0}: J5.57, U16.4 (O0)
/ram/~BKE_{1}: J6.57, U16.5 (O1)
/ram/~BKE_{2}: J7.57, U16.6 (O2)
/ram/~BKE_{3}: J9.57, U16.7 (O3)
/rom/~LS: U4.20 (~CS), U19.3
/rom/~US: U5.20 (~CS), U19.6
/~BG: U11.11 (BG), U14.2 (D)
/~HALT: J10.17, J11.17, J12.17, J13.17, J15.14, R6.2, U11.17 (HALT), U22.4
/~I_{1}: U11.24 (IPL1), U30.10
/~I_{2}: U11.23 (IPL2), U30.12
/~RES: J10.18, J11.18, J12.18, J13.18, J15.13, R5.2, U11.18 (RESET), U22.2, U25.4, U28.13
/~RIH: J1.57, J2.57, J3.57, J4.57, J8.3, R2.2, U16.13 (A1)
GND: C2.1, C3.1, C4.2, C8.1, C9.2, C10.2, C11.2, CB1.2, CB2.2, CB3.2, CB4.2, CB5.2, CB6.2, CB7.2, CB8.2, CB9.2, CB10.2, CB11.2, CB12.2, CB13.2, CB14.2, CB15.2, CB16.2, CB17.2, CB18.2, CB19.2, CB20.2, CB21.2, CB22.2, CB23.2, CB24.2, CB25.2, CB26.2, CB27.2, CB28.2, CB29.2, CB30.2, CB31.2, CB32.2, CB33.2, CB34.2, CB35.2, CB36.2, J1.4, J1.10, J1.16, J1.22, J1.28, J1.34, J1.40, J1.46, J1.52, J1.58, J2.4, J2.10, J2.16, J2.22, J2.28, J2.34, J2.40, J2.46, J2.52, J2.58, J3.4, J3.10, J3.16, J3.22, J3.28, J3.34, J3.40, J3.46, J3.52, J3.58, J4.4, J4.10, J4.16, J4.22, J4.28, J4.34, J4.40, J4.46, J4.52, J4.58, J5.4, J5.10, J5.16, J5.22, J5.27, J5.28, J5.30, J5.34, J5.40, J5.46, J5.50, J5.51, J5.52, J5.58, J6.4, J6.10, J6.16, J6.22, J6.27, J6.28, J6.30, J6.34, J6.40, J6.46, J6.50, J6.51, J6.52, J6.58, J7.4, J7.10, J7.16, J7.22, J7.27, J7.28, J7.30, J7.34, J7.40, J7.46, J7.50, J7.51, J7.52, J7.58, J8.4, J8.10, J8.16, J8.22, J8.28, J8.34, J8.40, J8.46, J8.52, J8.58, J9.4, J9.10, J9.16, J9.22, J9.27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
unnamed: C1.1, U27.6
unnamed: C1.2, R11.1, U22.5
unnamed: C5.2, R14.2, U25.1
unnamed: C7.1, U17.6
unnamed: C7.2, R21.2, U28.12
unnamed: C10.1, R16.2, SW2.3, U27.1
unnamed: D1.1 (K), R20.1
unnamed: C6.1, J16.1, R17.1, U27.4
unnamed: JP1.1 (A), U14.11 (C), X1.5 (OUT)
unnamed: JP1.3 (B), U14.9 (Q)
unnamed: JP2.1 (A), U22.6
unnamed: Q1.2 (B), R19.2
unnamed: C8.2, Q1.1 (C), R18.2, U30.5
unnamed: R12.1, U30.2
unnamed: R17.2, RV1.1
unnamed: R19.1, U30.4
unnamed: J14.1, SW1.3 (C)
unnamed: C9.1, RV1.2, SW3.2 (B), U27.3
unnamed: U11.10 (DTACK), U17.12
unnamed: U12.1 (G), U23.3
unnamed: U12.19 (P=R), U28.10
unnamed: U13.3 (I1a), U13.6 (I1b), U19.11
unnamed: U14.4 (~S), U28.11
unnamed: U14.8 (~Q), U14.12 (D)
unnamed: U16.1 (E), U16.10 (O2)
unnamed: U17.4, U23.1
unnamed: U17.10, U23.9
unnamed: U17.11, U28.3
unnamed: U21.6, U25.9
unnamed: U21.8, U25.10
unnamed: U21.13, U25.8
unnamed: U22.1, U22.3, U27.2
unnamed: U23.2, U23.6
unnamed: C2.2, R12.2, U24.11 (Cp)
unnamed: U24.2 (Q0), U29.2 (A0)
unnamed: U24.5 (Q1), U29.3 (A1)
unnamed: U24.6 (Q2), U29.4 (A2)
unnamed: U24.9 (Q3), U29.5 (A3)
unnamed: U24.12 (Q4), U29.6 (A4)
unnamed: U24.15 (Q5), U30.11
unnamed: U24.16 (Q6), U30.13
unnamed: U24.1 (~Mr), U25.3
unnamed: U25.2, U25.6
unnamed: U25.5, U30.6
unnamed: C6.2, R15.2, U26.1 (G1)
unnamed: U29.1 (G1), U29.19 (G2), U30.8

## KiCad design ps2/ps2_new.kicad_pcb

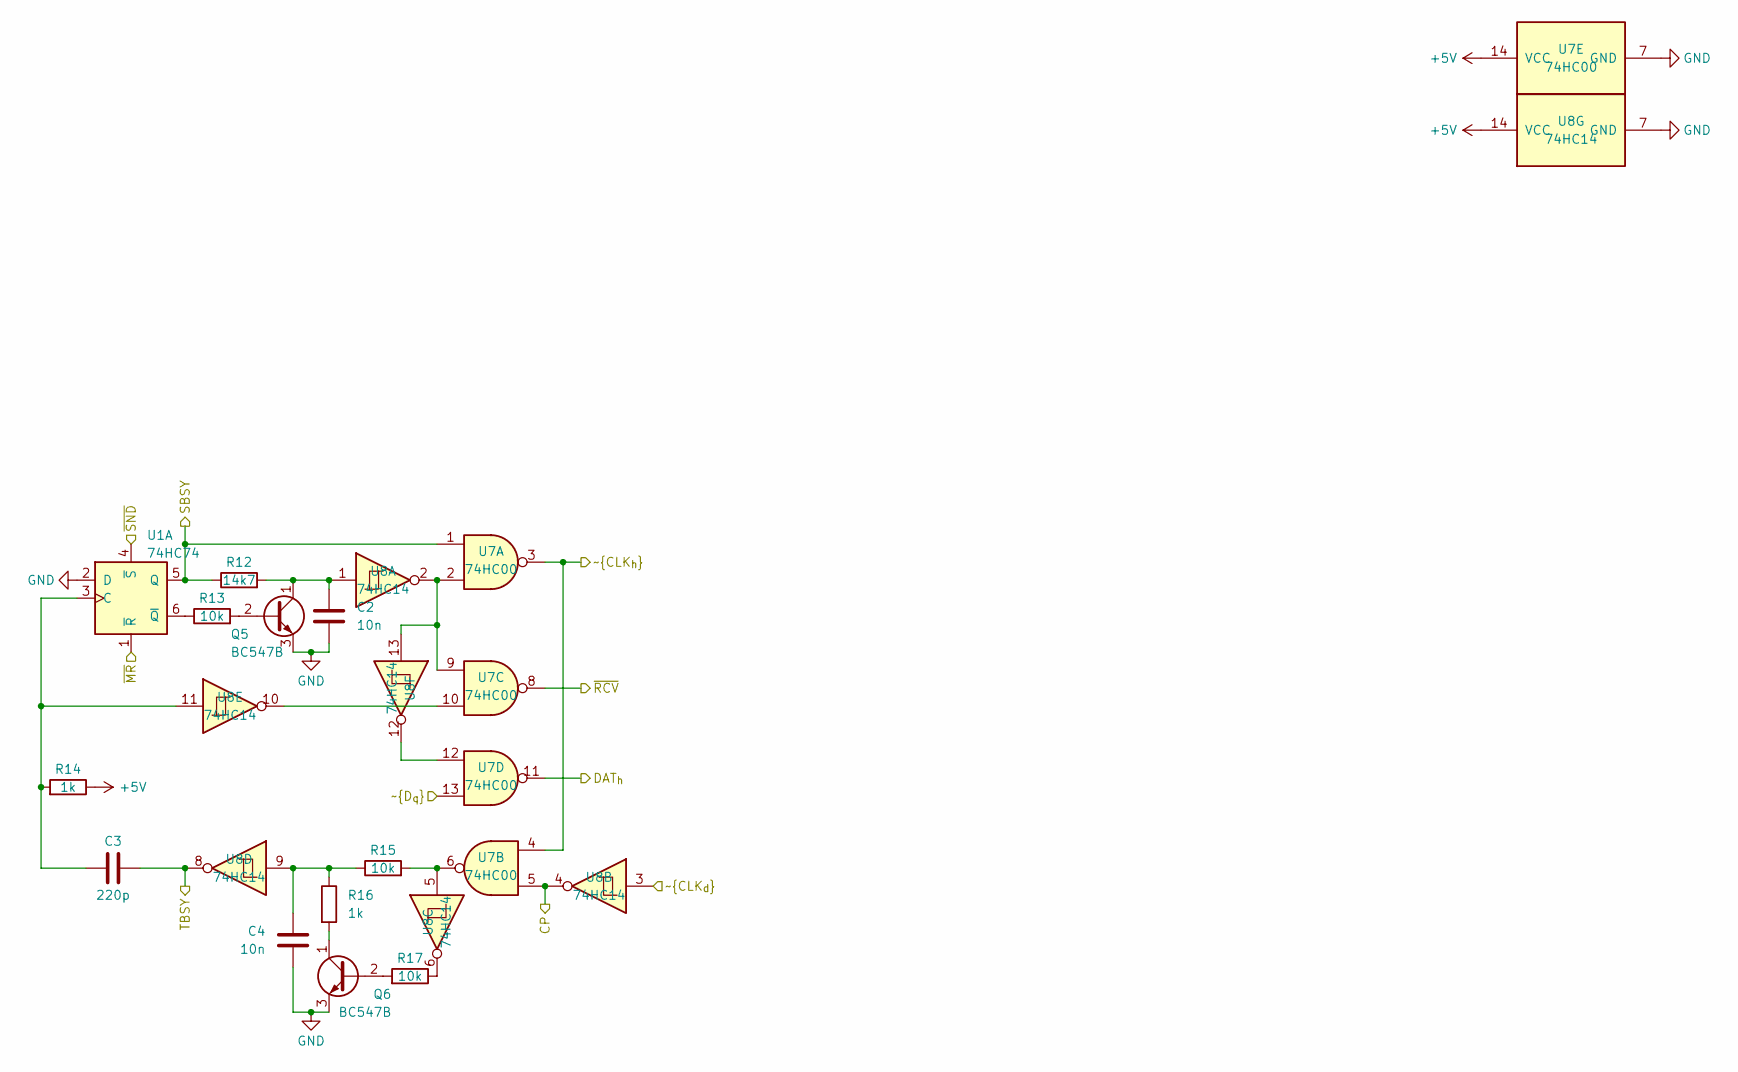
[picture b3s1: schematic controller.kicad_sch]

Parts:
C2, C4: 10n; C_Disc_D3.0mm_W1.6mm_P2.54mm
C3: 220p; C_Disc_D3.0mm_W1.6mm_P2.54mm
Q5, Q6: BC547B; TO-92
R12: 14k7; R_Axial_DIN0207_L6.3mm_D2.5mm_P2.54mm_Vertical
R13, R15, R17: 10k; R_Axial_DIN0207_L6.3mm_D2.5mm_P2.54mm_Vertical
R14, R16: 1k; R_Axial_DIN0207_L6.3mm_D2.5mm_P2.54mm_Vertical
U1: 74HC74; DIP-14_W7.62mm
U7: 74HC00; DIP-14_W7.62mm
U8: 74HC14; DIP-14_W7.62mm

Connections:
+5V: R14.1, U7.14 (VCC), U8.14 (VCC); also elsewhere on the board
/CP: U7.5, U8.4; also elsewhere on the board
/DAT_{h}: U7.11; also elsewhere on the board
/SBSY: R12.1, U1.5 (Q), U7.1; also elsewhere on the board
/TBSY: C3.2, U8.8; also elsewhere on the board
/~CLK_{d}: U8.3; also elsewhere on the board
/~CLK_{h}: U7.3, U7.4; also elsewhere on the board
/~D_{q}: U7.13; also elsewhere on the board
/~RCV: U7.8; also elsewhere on the board
/~RES: U1.1 (~R); also elsewhere on the board
/~W: U1.4 (~S); also elsewhere on the board
GND: C2.2, C4.2, Q5.3 (E), Q6.3 (E), U1.2 (D), U7.7 (GND), U8.7 (GND); also elsewhere on the board
unnamed: C4.1, R15.1, R16.1, U8.9
unnamed: Q5.2 (B), R13.2
unnamed: C2.1, Q5.1 (C), R12.2, U8.1
unnamed: Q6.2 (B), R17.2
unnamed: Q6.1 (C), R16.2
unnamed: R15.2, U7.6, U8.5
unnamed: R17.1, U8.6
unnamed: C3.1, R14.2, U1.3 (C), U8.11
unnamed: R13.1, U1.6 (~Q)
unnamed: U7.2, U7.9, U8.2, U8.13
unnamed: U7.10, U8.10
unnamed: U7.12, U8.12

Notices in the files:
SF68.kicad_pcb:
Copyright © 2025
